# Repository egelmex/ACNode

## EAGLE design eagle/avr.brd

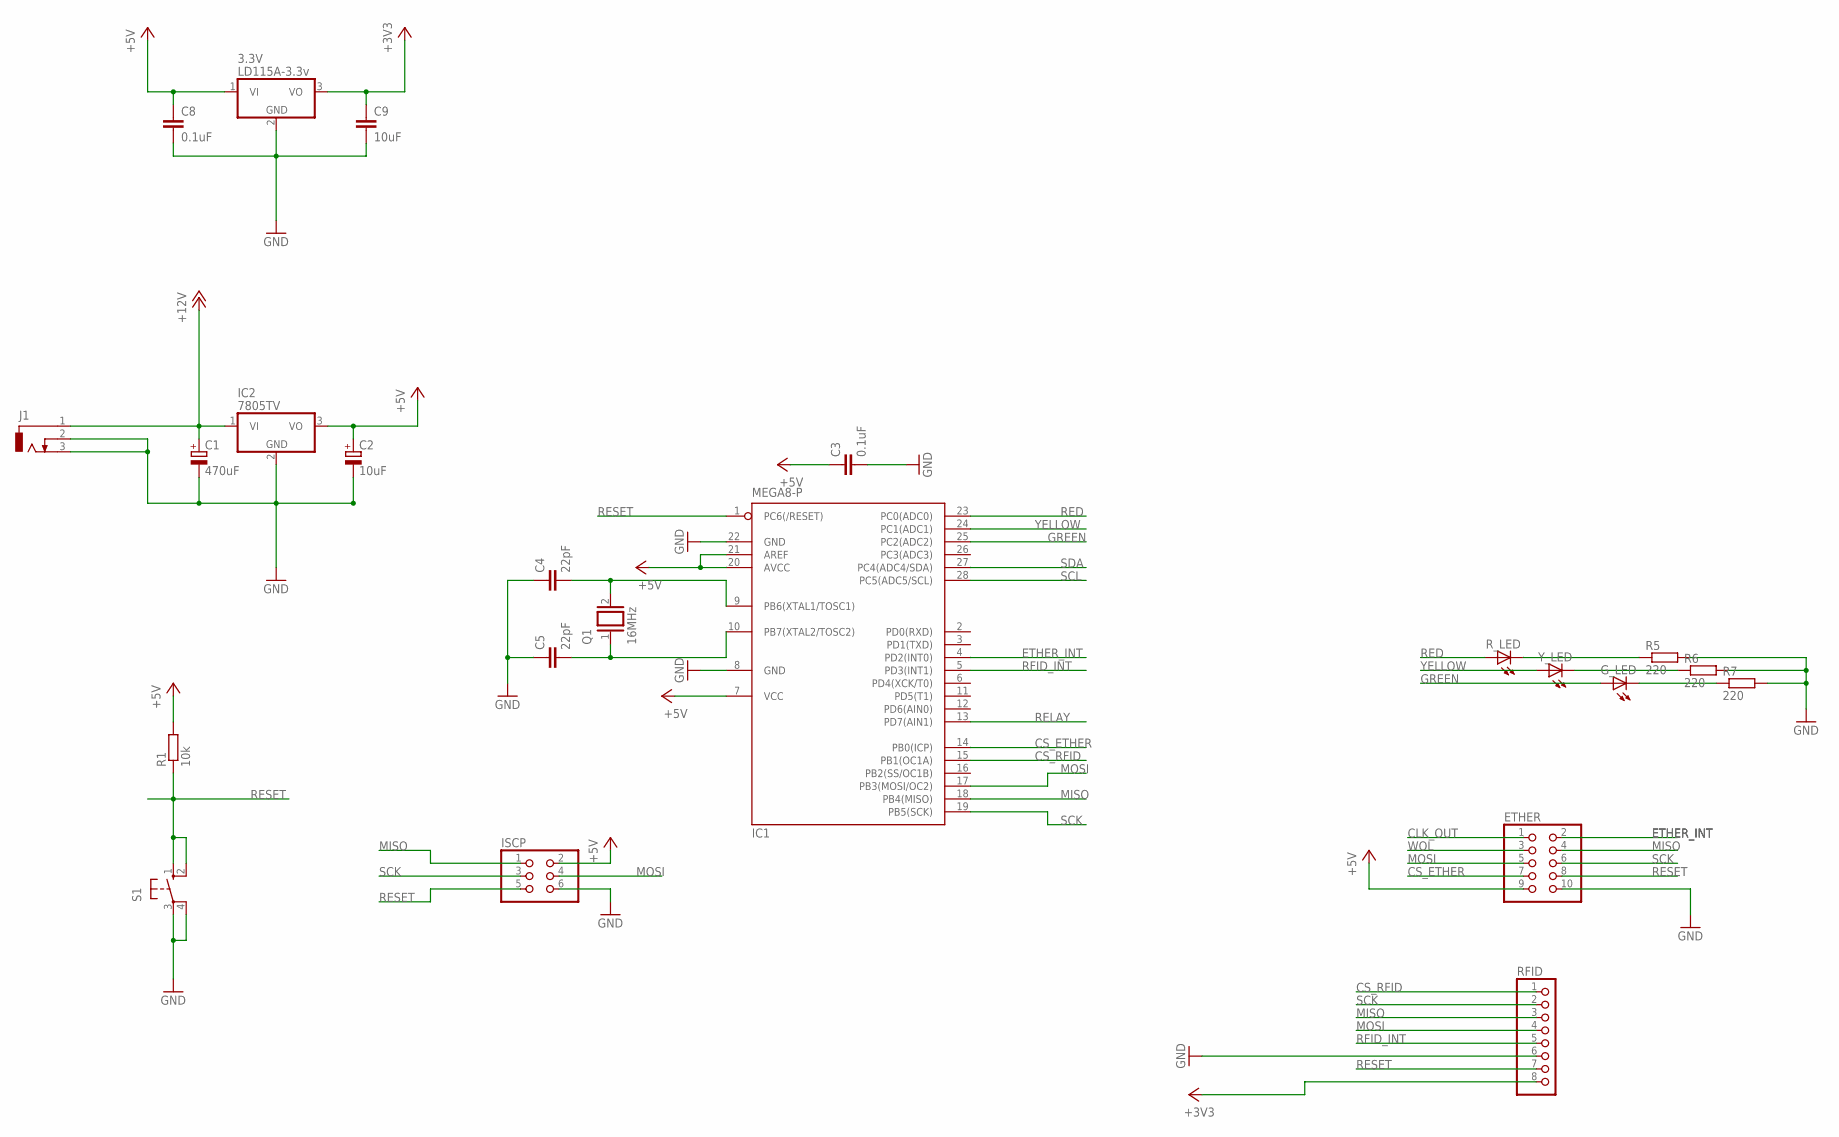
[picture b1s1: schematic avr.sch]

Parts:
3.3V: LD115A-3.3v; TO220V
C1: 470uF; E3,5-10
C2: 10uF; E3,5-10
C3, C8: 0.1uF; C050-025X075
C4, C5: 22pF; C050-025X075
C9: 10uF; C050-025X075
ETHER: PINHD-2X5; 2X05
G_LED: LED5MM
IC1: MEGA8-P; DIL28-3
IC2: 7805TV; TO220V
ISCP: PINHD-2X3; 2X03
J1: DCJ0303
Q1: 16MHz; QS
R1: 10k; 0207/10
R5, R6, R7: 220; 0207/10
RFID: PINHD-1X8; 1X08
R_LED: LED5MM
S1: 10-XX; B3F-10XX
Y_LED: LED5MM

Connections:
+3V3: 3.3V.3 (VO), C9.1, RFID.8
+5V: 3.3V.1 (VI), C2.+, C3.1, C8.1, ETHER.9, IC1.7 (VCC), IC1.20 (AVCC), IC1.21 (AREF), IC2.3 (VO), ISCP.2, R1.2
+12V: C1.+, IC2.1 (VI), J1.1
CLK_OUT: ETHER.1
CS_ETHER: ETHER.7, IC1.14 (PB0(ICP))
CS_RFID: IC1.15 (PB1(OC1A)), RFID.1
ETHER_INT: ETHER.2, IC1.4 (PD2(INT0))
GND: 3.3V.2 (GND), C1.-, C2.-, C3.2, C4.1, C5.1, C8.2, C9.2, ETHER.10, IC1.8 (GND), IC1.22 (GND), IC2.2 (GND), ISCP.6, J1.2, J1.3, R5.2, R6.2, R7.2, RFID.6, S1.3, S1.4 (P1)
GREEN: G_LED.A, IC1.25 (PC2(ADC2))
MISO: ETHER.4, IC1.18 (PB4(MISO)), ISCP.1, RFID.3
MOSI: ETHER.5, IC1.17 (PB3(MOSI/OC2)), ISCP.4, RFID.4
unnamed: R5.1, R_LED.K (C)
unnamed: C4.2, IC1.9 (PB6(XTAL1/TOSC1)), Q1.2
unnamed: R6.1, Y_LED.K (C)
unnamed: C5.2, IC1.10 (PB7(XTAL2/TOSC2)), Q1.1
unnamed: G_LED.K (C), R7.1
RED: IC1.23 (PC0(ADC0)), R_LED.A
RELAY: IC1.13 (PD7(AIN1))
RESET: ETHER.8, IC1.1 (PC6(/RESET)), ISCP.5, R1.1, RFID.7, S1.1 (S), S1.2 (S1)
RFID_INT: IC1.5 (PD3(INT1)), RFID.5
SCK: ETHER.6, IC1.19 (PB5(SCK)), ISCP.3, RFID.2
SCL: IC1.28 (PC5(ADC5/SCL))
SDA: IC1.27 (PC4(ADC4/SDA))
WOL: ETHER.3
YELLOW: IC1.24 (PC1(ADC1)), Y_LED.A

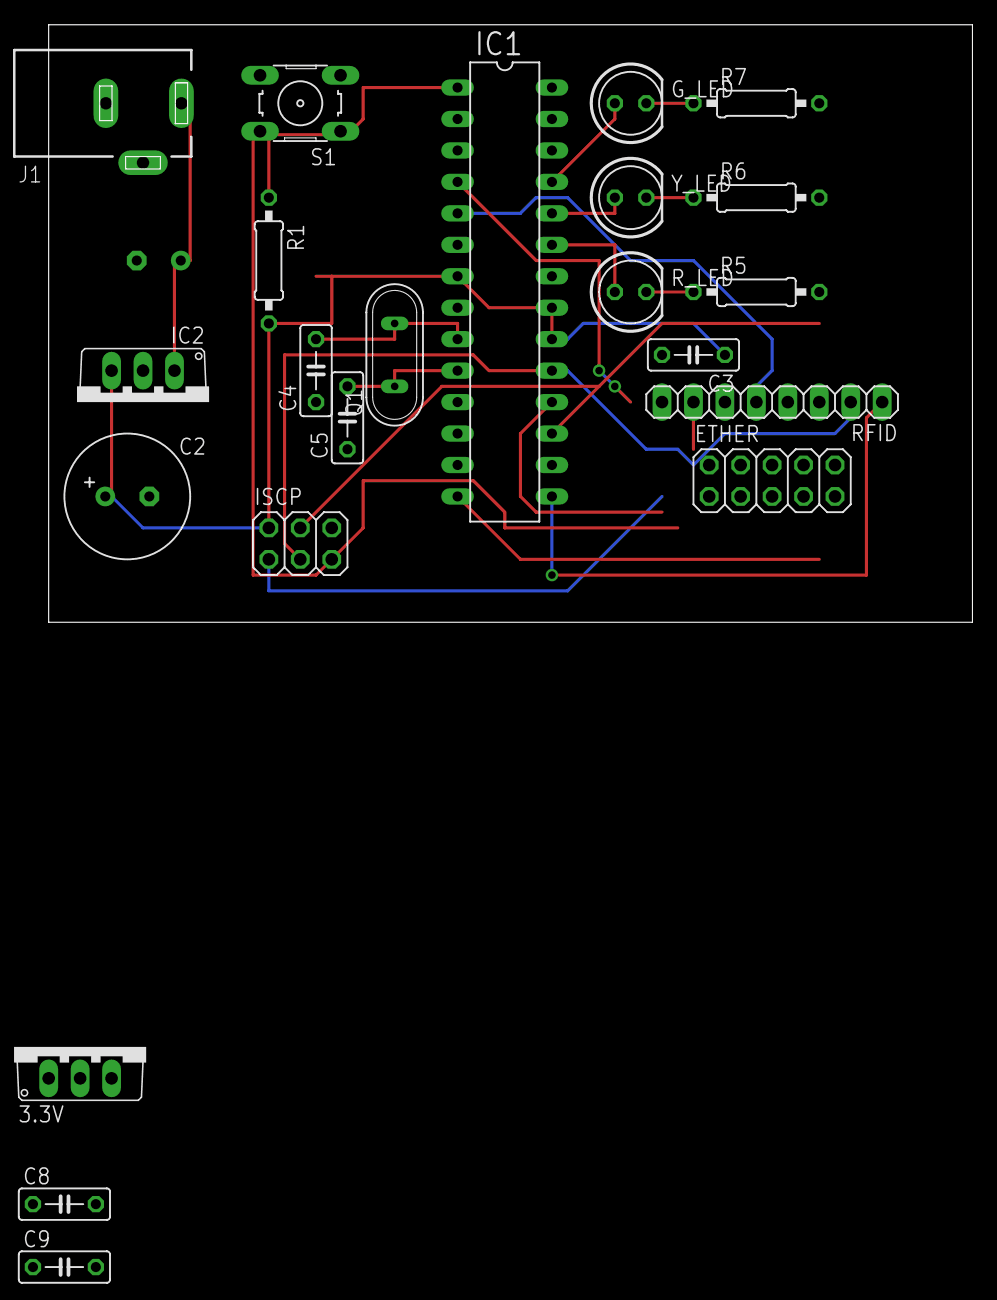
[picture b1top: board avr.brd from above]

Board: 2 copper layers, 74.6 x 48.2 mm, 23 parts (1 on the bottom side), 20 nets.

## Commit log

2014-04-13 intial commit
2014-04-30 switched to a design with no arduino
2014-05-01 Created EagleCAD Schematic :electric_plug:
    Currently only autorouted
    No Relay on in the design yet, or 3.3v reg
2014-05-01 Added 3.3v supply
2014-05-03 Fixed pin outs of modules
    Also added .gitignore to prevent git offering to track some binary files that
    Eagle creates in the background.
2014-05-03 Updated pinouts
